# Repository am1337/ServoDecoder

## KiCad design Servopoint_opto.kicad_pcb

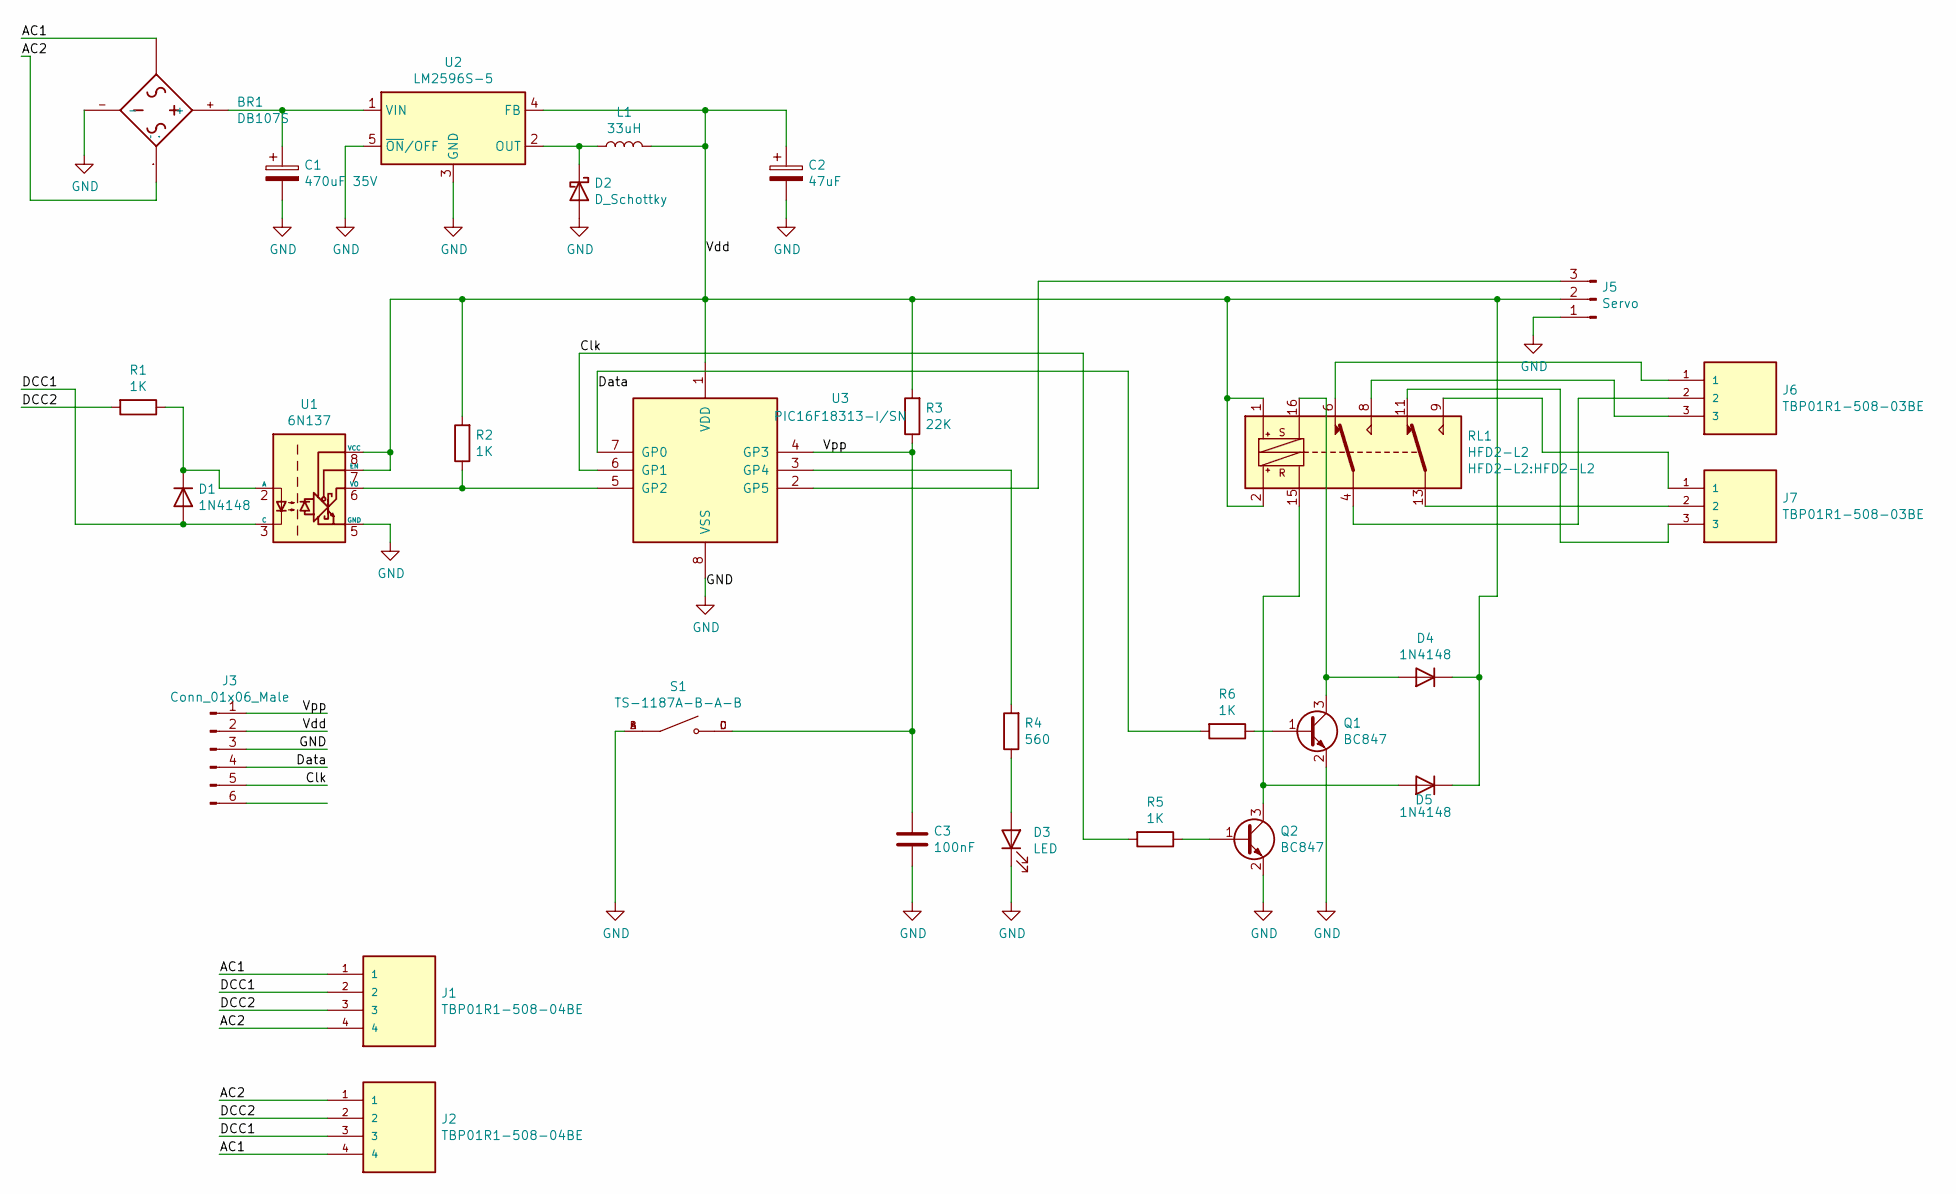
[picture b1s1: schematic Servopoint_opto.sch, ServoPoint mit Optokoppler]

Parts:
BR1: DB107S; DIOB_DB107S
C1: 470uF 35V; C_Elec_10x10.2
C2: 47uF; CP_EIA-6032-28_Kemet-C
C3: 100nF; C_1206_3216Metric
D1, D4, D5: 1N4148; D_SOD-123
D2: D_Schottky; D_SMA
D3: LED; LED_0805_2012Metric
J1, J2: TBP01R1-508-04BE; CUI_TBP01R1-508-04BE
J3: Conn_01x06_Male
J5: Servo; PinHeader_1x03_P2.54mm_Vertical
J6, J7: TBP01R1-508-03BE; CUI_TBP01R1-508-03BE
L1: 33uH; L_12x12mm_H8mm
Q1, Q2: BC847; SOT-23
R1, R2, R5, R6: 1K; R_0603_1608Metric
R3: 22K; R_0603_1608Metric
R4: 560; R_0603_1608Metric
RL1: HFD2-L2
S1: TS-1187A-B-A-B; SW_TS-1187A-B-A-B; PARTREV A0
U1: 6N137; SSO-8_6.7x9.8mm_P2.54mm_Clearance8mm
U2: LM2596S-5; TO-263-5_TabPin3
U3: PIC16F18313-I/SN; SOIC-8-1EP_3.9x4.9mm_P1.27mm_EP2.514x3.2mm

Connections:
/AC1: BR1.~, J1.1, J2.4
/AC2: BR1.~., J1.4, J2.1
/Clk: J3.5, R5.2, U3.6 (GP1)
/DCC1: D1.2 (A), J1.2, J2.3, U1.3 (C)
/DCC2: J1.3, J2.2, R1.2
/Data: J3.4, R6.2, U3.7 (GP0)
/Vdd: C2.1, D4.1 (K), D5.1 (K), J3.2, J5.2, L1.2, R2.2, R3.2, RL1.1, RL1.2, U1.7 (EN), U1.8 (VCC), U2.4 (FB), U3.1 (VDD)
/Vpp: C3.1, J3.1, R3.1, S1.C, S1.D, U3.4 (GP3)
GND: BR1.-, C1.2, C2.2, C3.2, D2.2 (A), D3.1 (K), J3.3, J5.1, Q1.2 (E), Q2.2 (E), S1.A, S1.B, U1.5 (GND), U2.3 (GND), U2.5 (~ON~/OFF), U3.8 (VSS)
unnamed: BR1.+, C1.1, U2.1 (VIN)
unnamed: D1.1 (K), R1.1, U1.2 (A)
unnamed: D2.1 (K), L1.1, U2.2 (OUT)
unnamed: D3.2 (A), R4.1
unnamed: D4.2 (A), Q1.3 (C), RL1.16
unnamed: D5.2 (A), Q2.3 (C), RL1.15
unnamed: J5.3, U3.2 (GP5)
unnamed: J6.1, RL1.6
unnamed: J6.2, RL1.4
unnamed: J6.3, RL1.8
unnamed: J7.1, RL1.9
unnamed: J7.2, RL1.13
unnamed: J7.3, RL1.11
unnamed: Q1.1 (B), R6.1
unnamed: Q2.1 (B), R5.1
unnamed: R2.1, U1.6 (VO), U3.5 (GP2)
unnamed: R4.2, U3.3 (GP4)

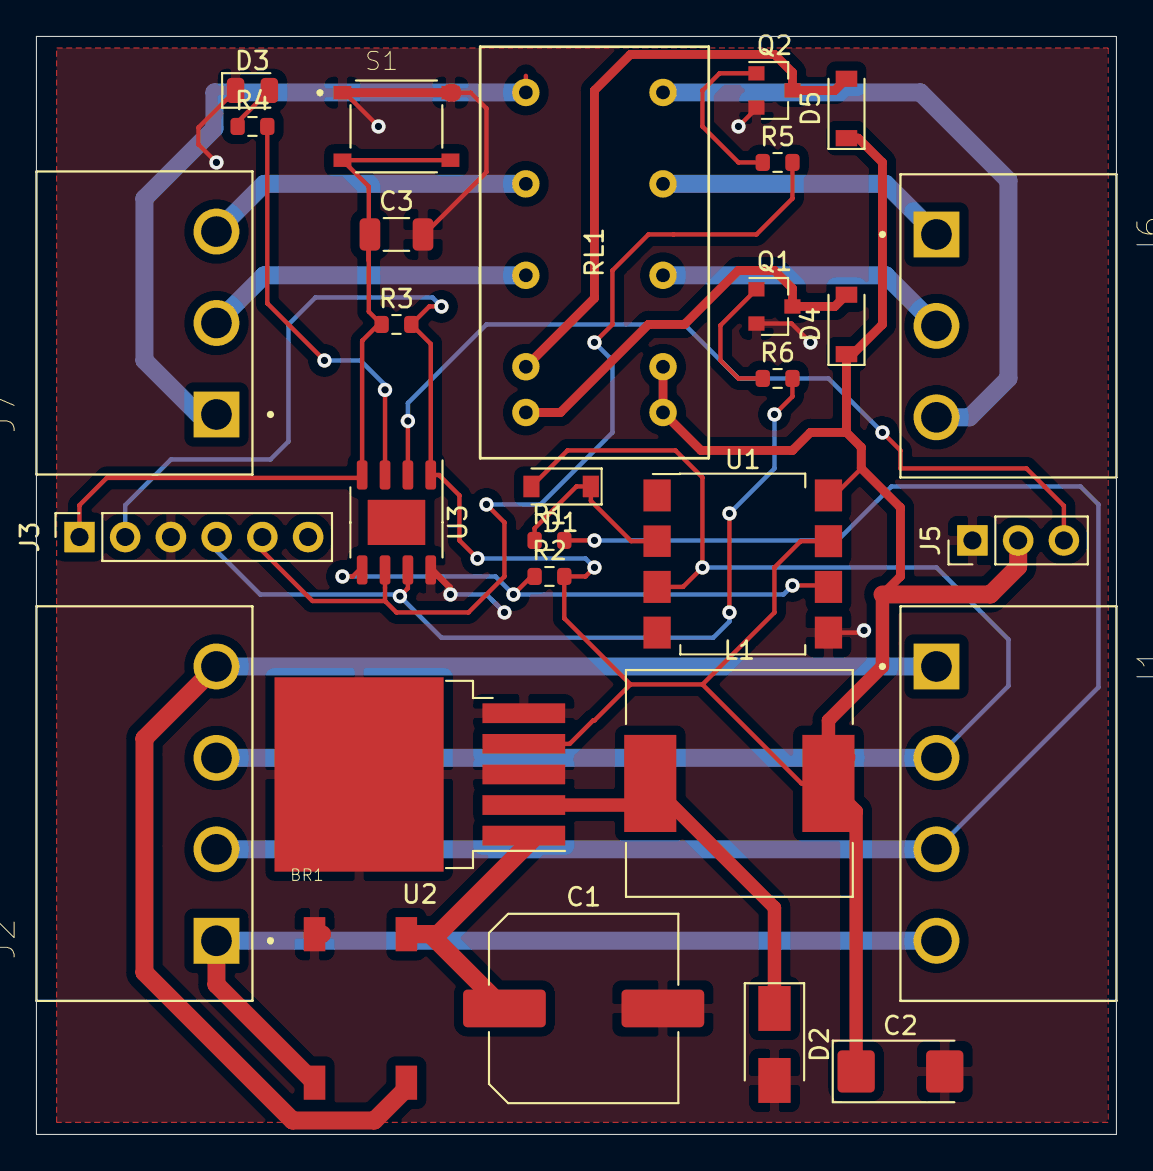
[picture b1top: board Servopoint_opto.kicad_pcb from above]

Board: 2 copper layers, 60.0 x 61.0 mm, 29 parts (0 on the bottom side), 26 nets.

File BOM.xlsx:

Comment | Designator | Footprint | LCSC Part #
DB107S | BR1 | DBS | C5377
470uF 35V | C1 | SMD-ECAP-10x10 | C249931
47uF | C2 | CASE-C_6032 | C145123 | x
100nF | C3 | CASE-A_3216 | C122257 | x
1N4148W | D1, D4, D5 | SOD-123 | C81598
SS54 | D2 | SMA,DO-214AC | C22452
LED | D3 | LED_0805 | C72037
2EDGRC-5.08-04P-14-100A(H) | J1, J2 | CONN-TH_2EDGRC-5.08-04P-14-100A_H | C669316
PZ200V-11-05P | J3 | HDR-TH_5P-P2.00-V-M | C541859
PZ200V-11-03P | J5 | HDR-TH_3P-P2.00-V-M | C541857
2EDGRC-5.08-03P-14-100A(H) | J6, J7 | CONN-TH_2EDGRC-5.08-03P-14-100A_H | C669315
33uH | L1 | SMD-12.0x12.0x8 | C167264
BC847A | Q1, Q2 | SOT-23-3 | C397577
1KΩ | R1, R2, R5, R6 | 0603 | C21190
22KΩ | R3 | 0603 | C31850
560Ω | R4 | 0603 | C23204
HFD2/005-M-L2 | RL1 | RELAY-TH_HFD2_+_X-X-L2-X | C399485
TS-1187A-B-A-B | S1 | SMD-SW-4_5.1x5.1x1.5 | C318884
6N137S1(TA) | U1 | SMD-8_6.6x9.8x2.54P | C110020
LM2596SX-5.0/NOPB | U2 | TO-263-5 | C10002
PIC16F18313-I/SN | U3 | SOIC-8_150mil | C150840

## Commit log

2021-10-05 changed pcb to 6 pin socket to programm pic via pickit 3, BOM and partnumber not updated yet, pcb not tested yet
2021-11-07 added image of decoder
